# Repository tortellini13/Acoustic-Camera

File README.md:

# Acoustic-Camera
DIY Open source acoustic camera using a beamforming array of microphones (WIP)

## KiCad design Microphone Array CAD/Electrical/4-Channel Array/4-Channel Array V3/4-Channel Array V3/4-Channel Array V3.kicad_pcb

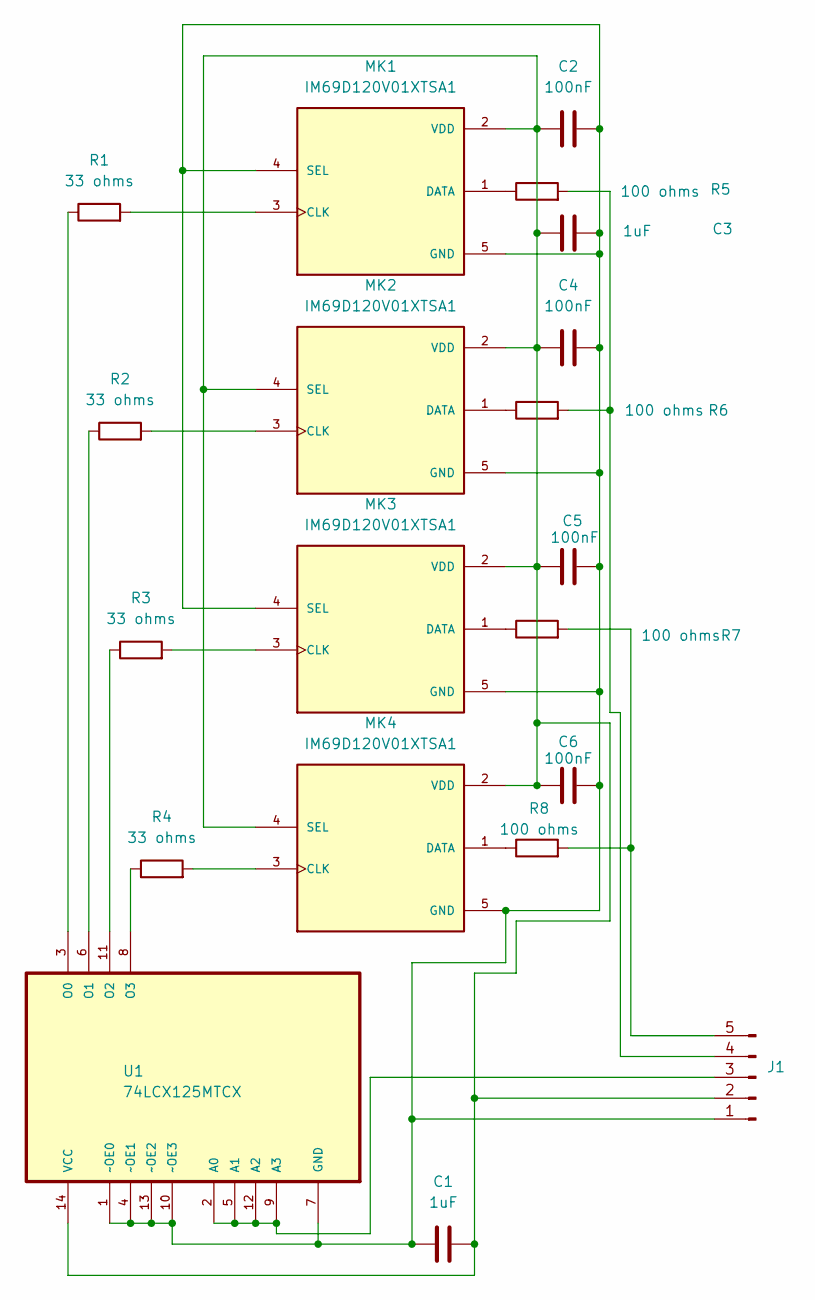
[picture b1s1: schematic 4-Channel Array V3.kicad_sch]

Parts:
C1, C3: 1uF; R_0603_1608Metric
C2, C4, C5, C6: 100nF; C_0402_1005Metric
J1: Conn_01x05_Pin; JST_XH_B5B-XH-A_1x05_P2.50mm_Vertical
MK1, MK2, MK3, MK4: IM69D120V01XTSA1; XDCR_IM69D120V01XTSA1; PARTREV 1.0
R1, R2, R3, R4: 33 ohms; R_0603_1608Metric
R5, R6, R7, R8: 100 ohms; R_0603_1608Metric
U1: 74LCX125MTCX; SOP65P640X120-14N; MPN 74LCX125MTCX

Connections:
unnamed: C1.1, C2.2, C3.2, C4.2, C5.2, C6.2, J1.1, MK1.4 (SEL), MK1.5 (GND), MK2.5 (GND), MK3.4 (SEL), MK3.5 (GND), MK4.5 (GND), U1.1 (~OE0), U1.4 (~OE1), U1.7 (GND), U1.10 (~OE3), U1.13 (~OE2)
unnamed: C1.2, C2.1, C3.1, C4.1, C5.1, C6.1, J1.2, MK1.2 (VDD), MK2.2 (VDD), MK2.4 (SEL), MK3.2 (VDD), MK4.2 (VDD), MK4.4 (SEL), U1.14 (VCC)
unnamed: J1.3, U1.2 (A0), U1.5 (A1), U1.9 (A3), U1.12 (A2)
unnamed: J1.4, R5.2, R6.2
unnamed: J1.5, R7.2, R8.2
unnamed: MK1.3 (CLK), R1.2
unnamed: MK1.1 (DATA), R5.1
unnamed: MK2.3 (CLK), R2.2
unnamed: MK2.1 (DATA), R6.1
unnamed: MK3.3 (CLK), R3.2
unnamed: MK3.1 (DATA), R7.1
unnamed: MK4.3 (CLK), R4.2
unnamed: MK4.1 (DATA), R8.1
unnamed: R1.1, U1.3 (O0)
unnamed: R2.1, U1.6 (O1)
unnamed: R3.1, U1.11 (O2)
unnamed: R4.1, U1.8 (O3)

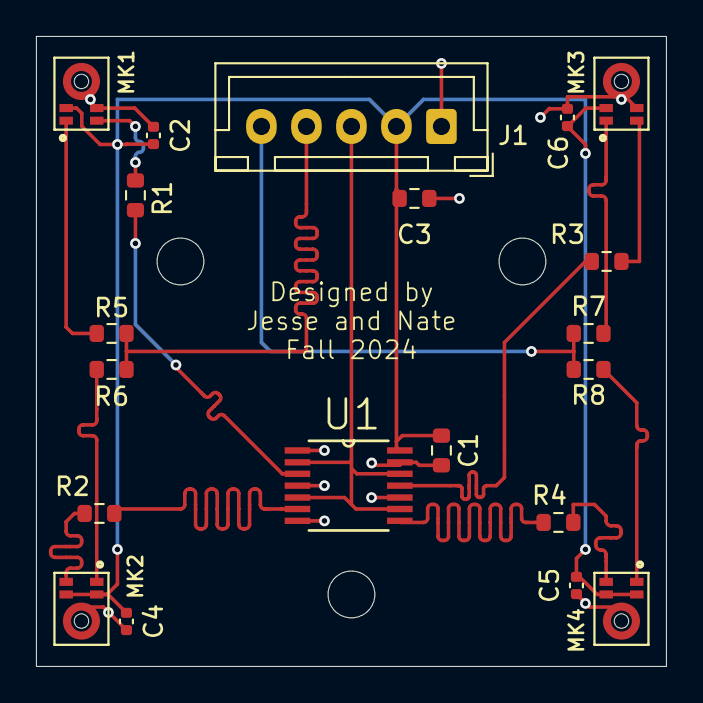
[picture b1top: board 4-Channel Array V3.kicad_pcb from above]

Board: 2 copper layers, 35.0 x 35.0 mm, 20 parts (0 on the bottom side), 17 nets.

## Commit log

2024-09-04 Signal processing and PARAMS
    Initial commit of main.cpp for the signal processing code and the PARAMS.h header
2024-09-04 Uploaded Visual
    Upload visual, rearrange files
2024-09-10 Created launch file and Makefile
2024-09-10 Updated Video.cpp
2024-09-11 Added Structure for Array Design
2024-09-11 Updated Array PCB
2024-09-12 Updated vscode for Pi
2024-09-12 Updated Makefile
2024-09-12 Continued development for Video
2024-09-12 Continued Array Development
2024-09-18 Video code Testing
2024-09-18 continued video code development
2024-09-19 Array v3
2024-09-20 Changed from double to float in audio code
2024-09-20 Restructured Audio and updated Makefile
2024-09-22 Video Code Development
2024-09-24 Restructure
2024-09-24 Edited Makefile
2024-09-24 Fixed Makefile
2024-09-25 Video
2024-09-25 Updated launch.cpp
2024-09-26 Integration of Shared Memory
2024-09-26 Added shm into audio
2024-09-26 Added error handling
2024-09-27 Cleaned up Video.cpp
2024-09-29 Updated Video
2024-10-01 Added shm for Configs to Video
2024-10-02 Changed 1-D shm to int and fixed inconsistent names
2024-10-04 Worked on CONFIGS SHM
2024-10-09 Added audio reading
2024-10-09 Updated PARAMS
2024-10-10 Initial video controls
2024-10-10 Added UHart Logo and Fab Files
2024-10-11 Restructured Audio
2024-10-14 Restructured shared memory
2024-10-15 Updated Audio
2024-10-17 Video might be working maybe not
2024-10-17 Cleaned up video
2024-10-21 Added Max value tracking, fixed annoying trackbar error
2024-10-21 Added Color Scale (in progress)
2024-10-21 Added text to color scale (in progress)
2024-10-22 Improved color scale
2024-10-22 Added alpha slider
2024-10-22 Rewrote sharedMemory.h
2024-10-23 Added FPS Counter
2024-10-23 Minor adjustments to video script
2024-10-23 Started optimizing video script
2024-10-24 Continued optimizing video script
2024-10-24 Worked on PI. It broke
2024-11-01 Rewored FFT and beamforming
2024-11-01 Worked on Audio
2024-11-06 Repaired Video Script
2024-11-06 Added Recording Functionality
2024-11-07 Idk at this point
2024-11-11 Restructured beamforming
2024-11-12 Changes from last week
2024-11-12 Added class to handle recording audio and started class for video
2024-11-12 Reorganization of Video
2024-11-13 Worked on video
2024-11-13 push!!!! push!!!!!!!
2024-11-16 Started refactoring Video
2024-11-19 Video is ready?
2024-11-20 push!!!!!!!!!
2024-11-22 Need to rewrite beamforming code :(
2024-11-25 Refactored code and added profiling tools
2024-11-25 All elements in
2024-11-27 FPS counter
2024-11-29 Optimized beamforming and expanded profiling
2024-12-03 Added debug messages to beamform
2024-12-03 video optimization in prog
2024-12-03 Optimization temporalily cancled
2024-12-03 IT DOING STUFF!!!
2024-12-03 video still broke
2024-12-04 Attempted frame polling
2024-12-04 Fixed audio interlacing
2024-12-06 Small edits
2024-12-09 Added automatic frame skipping for timing. It is still a mess though
2024-12-09 Small fixes
2024-12-09 Mild video cleanup
2024-12-09 Oops
2024-12-09 Fixed merge issues
2024-12-11 Beamforming in frequency doamin. Video multithreaded and different. Some shit still probably broken
2024-12-11 Something is happening?
2024-12-11 Kindof good now. still funky
2024-12-21 worked on delay and sum
2024-12-21 Reinetgration of video features in progress. Colorbar is still broken
2024-12-21 Repaired video after merge
2024-12-22 Cleaned up video and added more to Timer.h
2024-12-22 Fixed color scale, added FPS, began clamping
2024-12-23 Added clamping
2024-12-28 delay and sum (its boken)
2025-01-30 Changes from last year
2025-02-02 Added thresholding, repaired FPS, Test data in progress
2025-02-04 Implemented delay and sum. Needs optimization
2025-02-04 Megring
2025-02-04 more merging
2025-02-04 ummm
2025-02-04 More work on delay and sum. Opimization needed for beamform
2025-02-10 Optimized beaform
2025-02-11 More beamform optimizations
2025-02-11 added debug statements
2025-02-11 For nate
2025-02-12 Fixed beamform multithreading
2025-02-13 Optimized beamform. We're so close
2025-02-13 Added IMGUIIIIII
2025-02-13 some beamfrom stufff and merge
2025-02-18 Updated ImGUI, removed OpenCV Window
2025-02-18 OOOooOOOoO
2025-02-18 FFT is so broken
2025-02-18 reverted beamform changes
2025-02-20 uhhh video merge
2025-02-20 commiting to try and fix this
2025-02-20 Video working on pi with imgui!
2025-03-04 Worked on ALSA separate
2025-03-06 Autosave config, added image capture
2025-03-06 More stuff
2025-03-06 Update audio device name, modify config settings, and remove unused imgui.ini file
2025-03-11 Add initial imgui.ini configuration, adjust processing parameters, and update optimization flags
2025-03-13 Continued UI Development
2025-03-13 Remove imgui.ini configuration file, enable FFT printing, and refine beamforming calculations
2025-04-01 Small Changes
2025-04-02 Added STK, compiles, but is borked and cvtColor still no work
2025-04-03 Removed CVT
2025-04-03 Add configuration for UI windows, update save path, and adjust angle parameters
2025-04-06 uhhhh
2025-04-06 reverted video
2025-04-08 Artifact gone with new fft
2025-04-08 flipped it
2025-04-08 put a ring on it
2025-04-08 azimuth is screwey
2025-04-08 fft is normalized
2025-04-10 added wav file reading functionality
2025-04-10 trying phased array again
